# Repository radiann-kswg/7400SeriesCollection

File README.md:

# 7400 シリーズ汎用 IC Collection Database

7400 シリーズ汎用 IC の収集状況、購入履歴、データシート収集状況を管理する JSON データベースです。

## 📋 プロジェクト概要

このリポジトリは以下の目的で運用されています：

- **コレクション管理**: 入手済み IC の記録と管理
- **在庫追跡**: 所持している IC 型番の一覧化
- **購入計画支援**: レア度別の購入予定リスト
- **データシート管理**: メーカー別データシートの収集状況追跡
- **回路設計ナレッジベース**: 実際の使用例・回路設計情報の蓄積
- **汎用型番チートシート**: `74xNN` ごとの要点・注意点・一次資料確認の導線

## 🗂️ ディレクトリ構造

```
7400SeriesCollection/
├── overview/                             # overview系データ
│   ├── 7400_series_ic_overview.json      # マスターデータ：全IC情報
│   └── categories/                       # 上記マスタを論理分類で分割したJSON群
├── datasheets/                           # データシート管理
│   ├── 7400_series_ic_datasheet_collection_status.json
│   └── _download/                        # ダウンロード済みPDF保管
│       ├── FAIRCHILD(FairchildSemiconductor)/
│       ├── PHILIPS(NXPSemiconductors)/
│       ├── RENESAS/
│       ├── TI(TexasInstruments)/         # 型番プレフィックス別（直下に PDF は置かない）
│       │   ├── CD74HC/
│       │   ├── SN74/                     # 無印（標準 TTL）
│       │   └── SN74{ABT,AHC,ALS,AS,F,HC,LS,S}/
│       ├── TOSHIBA/
│       └── UTC(UnisonicTechnologies)/
├── getstarting/                          # 入手・購入管理【git 管理外】
│   ├── 7400_series_ic_collection_acquisition_history.json
│   ├── 7400_series_ic_purchase_plan_normal_or_lower.json
│   ├── 7400_series_ic_purchase_plan_rare.json
│   ├── 7400_series_ic_purchase_plan_maniac.json
│   └── 7400_series_ic_purchase_wishlist_very_nerd.json
├── scripts/                              # 自動化スクリプト
│   ├── autofill_gottenitems.py          # データシート情報自動同期
│   ├── merge_fp.py                      # データ統合処理
│   ├── refine_descriptions.py           # 説明文洗練化
│   ├── split_overview_by_logic_category.py # overviewを論理分類で分割
│   └── sort_datasheet_by_partnumber.py  # データシートソート
├── structures/                           # 【サブモジュール】回路構造資料（7400SeriesStructures）
└── usage/                                # 回路設計実例
  ├── 06_encoders_decoders/             # カテゴリ
  │   └── 74x141/                       # パーツ番号
  │       ├── 74x141.md                 # チートシート（自動生成）
  │       └── 01_simple_nixie_tube_demo.md  # 実回路例（手書き）
  └── A_combinated_samples/
    └── 74x181,182/                   # 複数IC連携サンプル（カンマ区切り）
```

## 📊 データファイル説明

### マスターデータ

#### `overview/7400_series_ic_overview.json`

全 7400 シリーズ IC の基本情報を格納するマスターデータベース。

```json
{
  "PartNumber": "74x00",
  "Description": "Quad 2-input NAND gate",
  "Description_JP": "4回路2入力NANDゲート",
  "Rarity": "Commons"
}
```

**レア度分類**:

- **一般流通品**: `Commons`, `Normal`, `Normal+`, `Rare`, `SuperRare`
- **廃止品/特殊品**: `Abolition(R+)`, `Maniac(SR+)`, `ManiacRare(SSR)`, `VeryNerd(UR)`

### 入手管理データ

> **⚠️ `getstarting/` は git 管理外です。** 購入先・コメントを含む私物情報のため、データシート PDF と同様に `.gitignore` で除外しています。ファイルはローカルに存在し、参照するスクリプトはそのまま動作します。クローンしただけの環境では存在しません。

#### `getstarting/7400_series_ic_collection_acquisition_history.json`

実際に入手した IC の記録（購入先、コメント含む）。

```json
{
  "PartNumber": "74x00",
  "GetStartingECS_JP": ["秋月電子", "Amazon"],
  "Comments": ["Amazonの74HCシリーズICキットから入手"],
  "GottenItemsMN_CMOS": ["74HC00N", "SN74HC00N"],
  "GottenItemsMN_TTL": ["SN74S00N"],
  "GottenItemsMN_Other": []
}
```

### データシート管理

#### `datasheets/7400_series_ic_datasheet_collection_status.json`

各パーツのデータシート入手状況を追跡。

```json
{
  "PartNumber": "74x00",
  "GottenItems_MakerOfDataSheet": {
    "SN74HC00N": "TI(Texas Instruments)",
    "74HC00N": "(収集予定:NXP Semiconductors)",
    "74S00N": "(保留)"
  }
}
```

**ステータス表記**:

- `"メーカー名"`: データシート入手済み
- `"(収集予定:メーカー名)"`: 未入手、収集予定
- `"(保留)"`: 収集保留中

## 🔧 スクリプト使用方法

### Python 開発環境とテスト

リポジトリルートで Python 3.14 の仮想環境を作成します。データ管理と PDF 処理の依存関係は `requirements.txt` に固定しています。基板配置に使う `pcbnew` と KiKit は KiCad 側の Python 環境で実行します。

**Windows（PowerShell）**。Python 本体を Codex からも読める場所に置くには、初回に Python Install Manager で次を実行します。

```powershell
py install --target=.venv/base 3.14
.\.venv\base\python.exe -m venv .venv
.\.venv\Scripts\python.exe -m pip install -r requirements.txt
```

作成済みの環境では、Codex・Copilot ともに次のコマンドでテストできます。VS Code の Python 拡張で別の環境が選択されている場合は、「Python: Select Interpreter」でこの実行ファイルを選択してください。

```powershell
.\.venv\Scripts\python.exe -m unittest discover -s scripts -v
```

**Linux（Codex・GitHub Copilot）**。`python3` と `venv` が利用できる環境で実行します。

```sh
sh scripts/setup-dev.sh
.venv/bin/python -m unittest discover -s scripts -v
```

Codex のクラウド環境でセットアップコマンドを指定する場合は `sh scripts/setup-dev.sh` を登録します。GitHub Copilot のクラウドエージェントでは、既定ブランチの [セットアップワークフロー](.github/workflows/copilot-setup-steps.yml) が同じコマンドを実行します。テストには公開データと一時ディレクトリを使います。

### データシート情報の自動同期

入手履歴からデータシート収集状況を自動生成：

```bash
python3 scripts/autofill_gottenitems.py
```

### データ統合処理

レア度別購入予定 JSON の生成：

```bash
python3 scripts/merge_fp.py
```

### マスターデータの論理分類分割

Wikipedia の 7400 シリーズ機能分類を参考に、`overview/7400_series_ic_overview.json` を分類別 JSON に分割して `overview/categories/` に出力します。

```bash
python3 scripts/split_overview_by_logic_category.py
```

出力される分類ファイル（例）:

- `01_buffers_inverters.json`
- `02_nand_and_gates.json`
- `03_nor_or_gates.json`
- `04_xor_xnor_gates.json`
- `05_flipflops_latches.json`
- `06_encoders_decoders.json`
- `07_data_selectors_mux_demux.json`
- `08_counters.json`
- `09_registers.json`
- `10_arithmetic.json`
- `11_error_detection_correction.json`
- `12_memory_storage.json`
- `13_programmable_logic.json`
- `14_system_controllers_timing.json`
- `15_interfaces_links.json`
- `16_analog_mixed_signal.json`
- `99_other.json`

````

### VS Code タスク

VS Code から実行可能なタスク：

- **Generate FP/ALL JSONs**: データ統合処理
- **Refine Descriptions**: 説明文洗練化
- **Regenerate ALL after refine**: 洗練後の再生成

※ これらのタスクは `scripts/merge_fp.py` / `scripts/refine_descriptions.py` を実行します。

## 📝 メーカー型番接頭辞

| 接頭辞               | メーカー                            |
| -------------------- | ----------------------------------- |
| `SN74*`, `CD74*`     | TI (Texas Instruments)              |
| `U74*`               | UTC (Unisonic Technologies)         |
| `HD74*`              | RENESAS                             |
| `TC74*`              | TOSHIBA                             |
| `MM74*`, `MC74*`     | FAIRCHILD (Fairchild Semiconductor) |
| `74HC*` (接頭辞なし) | PHILIPS (NXP Semiconductors)        |

## 🔗 参照リソース

- [List of 7400-series integrated circuits - Wikipedia](https://en.wikipedia.org/wiki/List_of_7400-series_integrated_circuits)
- [AGENTS.md](AGENTS.md) - 詳細な開発ガイドライン（Codex・Claude・Copilot 共通の単一の正本）

## 📐 回路設計例の作成

`usage/`ディレクトリに実際の回路設計例を追加できます。

### ディレクトリ命名規則

```text
usage/
└── {カテゴリ名}/
  └── 74x{型番}/
    ├── 74x{型番}.md  # チートシート（自動生成）
    ├── 01_*回路名.md
    ├── 02_*回路名.md
    └── ...
````

## 🧾 汎用型番チートシート（usage/{カテゴリ名}/{74xNN}/{74xNN}.md）

`overview/7400_series_ic_overview.json` を元に、汎用型番（`74xNN`）ごとのチートシートを生成します。

- 入口: [usage/index.md](usage/index.md)
- 生成スクリプト: [scripts/generate_usage_cheatsheets.py](scripts/generate_usage_cheatsheets.py)

```bash
python3 scripts/generate_usage_cheatsheets.py
```

方針: ピン配置/真理値表/電気特性などの断定は一次資料が必要なため、未検証のまま書かない（リンクとチェックリスト中心）。

複数 IC 連携のシリーズは `usage/A_combinated_samples/74x181,182/` のようにカンマ区切りでまとめる。

### 必須記載項目

1. 回路概要
2. 回路の仕様
3. ピンアサインと配線方法
4. 必要部品リスト
5. 配線の注意事項
6. 表示器の対応（LED、7 セグ、ニキシー管等）
7. 動作確認手順
8. トラブルシューティング
9. 回路の拡張性

詳細は [AGENTS.md の回路設計ドキュメント作成ガイド](AGENTS.md#回路設計ドキュメント作成ガイドusage)を参照。

## 🔌 デモ基板の製作（`pcb-demo/`）

収集した現物の DIP IC をソケットに挿し、**その IC が実際に動いている状態**で展示する基板群。
「本物の元素を封入した周期表」の 7400 シリーズ版という位置づけ。

全タイルで回路トポロジは共通で、型番ごとに変わるのは**電源ピン配線・未実装セル・シルクの 3 点だけ**。
これにより、ピン機能表が未確定の型番でも「VCC/GND のピン位置とピン数」さえ一次資料で確認すれば設計できる。

| ドキュメント | 内容 |
|---|---|
| [`pcb-demo/REQUIREMENTS.md`](pcb-demo/REQUIREMENTS.md) | 要件定義（決定事項・制約・段階計画・非目標・リスク） |
| [`pcb-demo/_carrier/README.md`](pcb-demo/_carrier/README.md) | 共通キャリア設計仕様（回路方式・定数・命名規則・生成規則） |
| [`pcb-demo/ORDER_CHECKLIST.md`](pcb-demo/ORDER_CHECKLIST.md) | JLCPCB 発注チェックリスト（発注ゲート） |
| [`pcb-demo/index.md`](pcb-demo/index.md) | 型番別 KiCAD プロジェクト一覧 |

## 🛡️ データ整合性の維持

このプロジェクトは複数の JSON ファイル間で整合性を保つ必要があります：

- **PartNumber**: すべてのファイルで`74x`形式を使用
- **文字エンコーディング**: UTF-8 を厳守
- **配列順序**: PartNumber 昇順を維持
- **型番表記**: 汎用表記（`74x00`）と実際の型番（`SN74HC00N`）を区別

## 🚫 禁止事項

1. 既存データの意図しない改変
2. PartNumber 体系の破壊（`74x`形式の維持）
3. 文字コードの変更（UTF-8 厳守）
4. JSON スキーマの勝手な変更
5. ファイル間の不整合を引き起こす操作

## 📄 ライセンス

MIT License（[LICENSE](LICENSE)）。

**ハードウェア設計データ（`pcb-demo/` 配下の KiCAD プロジェクト・Gerber・BOM を含む）も同じく MIT License** で提供します。

---

**管理者**: radiann-kswg
**最終更新**: 2026 年 2 月 14 日

```

```

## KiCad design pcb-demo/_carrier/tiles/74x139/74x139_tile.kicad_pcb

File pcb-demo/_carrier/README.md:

# 共通キャリア設計仕様（Specimen Tile v0.1）

全タイルで共通の回路トポロジ。型番ごとに変わるのは**電源ピン配線・未実装セル・シルクの 3 点だけ**（→ [`../REQUIREMENTS.md`](../REQUIREMENTS.md) §2.3）。

- 版: 0.8（2026-11-22: プルアップ LED セル（active_low / open_collector 出力）の +5V を裏面経由に変更（REQUIREMENTS D31）。クロックセルは接点 1・11 のみ（D30、R10））。0.7（2026-11-22: オープンコレクタ出力を赤 LED + プルアップ配線で表示（REQUIREMENTS D29））。0.6（2026-09-17: 入力接点の LED 表示を廃止しスイッチのみに変更（REQUIREMENTS D25）。2026-09-16: Rd を 220Ω に変更（旧 1kΩ、REQUIREMENTS D16）。LED を負論理=赤／通常=白の2色に変更（D22）。クロック入力クリーンアップ回路（タクトスイッチ+RC+74x1G14）を実装・DRC/ERC検証済み（REQUIREMENTS §4.2/D17・D24））
- 対象: DIP-14 / DIP-16 / DIP-20（300mil）= 所持品の 118/120

---

## 1. ブロック構成

```text
        +5V ──┬──────────────────────────────── 電源ピン（型番依存）
              │
             C1 100nF
              │
        GND ──┴──────────────────────────────── GND ピン（型番依存）

  ┌─ I/O セル（信号ピン 1 つあたり。最大 18 セル）──────────┐
  │                                                          │
  │   +5V ──o                                                │
  │          \  SW（SPDT）                                   │
  │   GND ──o  \___ Rd 1k ───┬─── ソケット接点 k ─── IC ピン │
  │                          │                               │
  │                          └─ Rled 4.7k ─ LED ─ GND        │
  └──────────────────────────────────────────────────────────┘
```

---

## 2. I/O セルの回路方式

### 2.1 採用案: SPDT スイッチ + 直列抵抗（プルダウン無し）

スイッチで入力を **+5V か GND のどちらかに必ず接続**し、間に 220Ω を挟む（旧 1kΩ、REQUIREMENTS D16）。

**この方式を採る理由（D10 からの変更）**: 要件定義 D10 で想定した「SPST スイッチ + 10kΩ プルダウン」は、**TTL ファミリで成立しない**。74LS の入力は L のとき最大 0.4mA を吐き出すため、10kΩ プルダウンでは入力電圧が 0.4mA × 10kΩ = 4V まで浮き、VIL(max) 0.8V を大きく超えて L と認識されない。SPDT なら L 側でも 1kΩ を介して GND に落ちるため 0.4V に収まり、**CMOS と TTL の両方が動く**。副次的に、プルダウン抵抗 18 本が不要になり部品点数もむしろ減る。

### 2.2 定数と動作点

| 記号   | 値    | 役割                     |
| ------ | ----- | ------------------------ |
| `Rd`   | 220 Ω | 入力駆動の直列抵抗（旧 1kΩ、D16） |
| `Rled` | 4.7 kΩ | LED 電流制限             |
| LED    | 0603 赤（高効率品） | 状態表示   |

計算（VCC = 5V、LED 順方向電圧 Vf ≈ 2.0V）:

| 条件                           | 結果      | 判定                                                |
| ------------------------------ | --------- | --------------------------------------------------- |
| スイッチ H 側（LED 負荷込み）  | 約 4.4V   | 74HC VIH 3.5V / 74LS VIH 2.0V を満たす              |
| スイッチ L 側（74LS の IIL 0.4mA、Rd=220Ω） | 約 0.09V  | VIL(max) 0.8V を満たす（旧 1kΩ では 0.4V。220Ω化でマージン拡大、S/H 系の大きい IIL にも対応、D16） |
| IC 出力が H のときの LED 電流  | 約 0.62mA | 高効率 LED なら室内で視認可。Phase 1 で実物調整     |
| **出力ピンのスイッチを誤操作したときの電流（Rd=220Ω）** | **約 22.7mA（公称）/ 約 25.1mA（Vcc+5%・R-5%の最悪条件）** | **要注意**: 74HC 絶対最大定格 ±25mA に対しほぼ余裕が無く、最悪条件では超過し得る。1% 級抵抗の使用、またはパイロットに含む各ファミリの個別データシートでの再確認を推奨（発注前の宿題） |

**安全規則**: `Rd` は**出力ピンや双方向ピンを誤って駆動したときの電流制限器を兼ねる**ため、**省略は禁止**。現行値は 220Ω固定（D16）で、上表の通り 74HC 絶対最大定格に対するマージンが小さいため、これより**低い値への変更は不可**（誤操作時の電流がさらに増える）。出力接点はスイッチと `Rd` を DNP にする（REQUIREMENTS D15）が、フットプリントは残す。

### 2.3 廉価案（TTL 非対応）

SPDT スイッチの単価が見積もりを圧迫する場合のみ、**SPST + 10kΩ プルダウン**に落とす。この場合 **TTL（LS/S/ALS/F/H）ファミリは動作対象外**となり、CMOS（HC/HCT/AC/ACT/AHC/LVC）専用になる。採否は Phase 1 の LCSC 価格確認で判断する。

---

## 3. 部品構成（1 タイル）

| Ref            | 部品                        | 数         | 実装       |
| -------------- | --------------------------- | ---------: | ---------- |
| `U1`           | DIP-20 ソケット 300mil       |          1 | **手はんだ** |
| `J1`           | 2 ピンヘッダ 2.54mm（+5V/GND） |          1 | **手はんだ** |
| `D1`–`D20`     | LED 0603（`active_low` 出力=赤 C2286 / 通常出力=白・部品番号未選定。D22） | 最大 18 | JLCPCB |
| `R1`–`R20`     | `Rled` 4.7kΩ 0603（C23162）   | 最大 18    | JLCPCB     |
| `R21`–`R40`    | `Rd` 220Ω 0603（部品番号未選定、実装確定時に選定。D16） | 最大 18 | JLCPCB |
| `SW1`–`SW20`   | SPDT スイッチ MSS12C02LS-BB2.0（C3008585） | 最大 18 | JLCPCB  |
| `C1`           | 100nF 0603（C14663）          |          1 | JLCPCB     |

SMD 実装点数は最大約 61。**抵抗を 4 素子アレイにまとめると 36 → 9 個に減り、合計約 34 点**になる（→ REQUIREMENTS §5）。アレイも Basic で揃うが、50×50mm では個別 0603 で収まったため現状は個別（REQUIREMENTS D14）。スイッチだけが Extended。

抵抗値は `Rled` と `Rd` の 2 種類のみ。部品種類を増やさないこと。

---

## 4. リファレンス指定子の命名規則

生成スクリプトが機械的に参照できるよう、**ソケット接点番号 k（1〜20）と 1 対 1 に対応させる**:

| 部品         | Ref     |
| ------------ | ------- |
| スイッチ     | `SWk`   |
| LED          | `Dk`    |
| `Rled`       | `Rk`    |
| `Rd`         | `R(20+k)` |
| ソケット接点 | `U1` パッド `k` |

例: 接点 7 → `SW7` / `D7` / `R7` / `R27` / `U1` パッド 7。

この規則を崩すと型番別生成（電源接点の差し替えと DNP 指定）が成立しないため、**手作業で振り直さないこと**。

---

## 5. 寸法・レイアウト規約

| 項目               | 値                                       |
| ------------------ | ---------------------------------------- |
| 外形               | 50 × 50 mm（100×100mm パネルに 2×2。REQUIREMENTS D9） |
| 層数 / 厚み / 銅箔 | 2 層 / 1.6mm / 1oz                       |
| 最小パターン幅     | 0.25mm（JLCPCB 下限 0.127mm には張り付かない） |
| 基板端クリアランス | 銅箔は端から 0.5mm 以上（V-cut 分離のため） |
| 実装面             | **上面のみ**（Economic 組立の制約）      |
| `U1` 配置          | タイル中央に横置き。ピン 1 を左下（接点 1〜10 が下段、20〜11 が上段） |
| `C1` 配置          | ソケット左の `J1` 横。標準配置の VCC（接点 20）から約 4mm。非標準の型番（§6.4）では離れる |
| I/O セル配置       | 接点 k の列を 4.6mm ピッチで並べる（下段は接点 1→10、上段は 20→11 を左から）。1 列は外周側から スイッチ → LED / `Rk` / `R(20+k)` → ソケットへの引き出し |
| 電源               | +5V は外周レール（上・下・左）とソケット下を通るバス。GND は裏面ベタ |
| シルク             | 各列のピン名（VCC/GND 含む）、型番・機能名（英・和）、給電表示。裏面に版・カテゴリ・ライセンス |

I/O セルは接点順に規則的に並べる。これにより自動配線が不要になり（→ REQUIREMENTS §9 R5）、シルクのピン名とも視覚的に対応する。

---

## 6. 型番別の生成規則

### 6.1 接点マッピング

n ピン IC をピン 1 側へ端寄せして挿入する前提:

```text
IC pin i  (i <= n/2)  ->  ソケット接点 i
IC pin i  (i >  n/2)  ->  ソケット接点 i + (20 - n)
```

### 6.2 差分の適用

| 差分         | 規則                                                                                     |
| ------------ | ---------------------------------------------------------------------------------------- |
| ① 電源接点   | 型番の VCC / GND ピンを §6.1 で接点に変換し、その接点を +5V / GND ベタに接続。**I/O セルは実装しない** |
| ② セル種別   | `pinspec/{型番}.json` の `dir` で決める。`input` → **スイッチのみ**（`Rk`・`Dk` を DNP、REQUIREMENTS D25）。`output` / `tri_state` → `SWk`・`R(20+k)` を DNP（LED のみ）。`open_collector` → LED のみで、`active_low` 出力と同じ赤 LED + プルアップ配線（点灯 = L、REQUIREMENTS D29）。`bidirectional` は D19 により生成停止。未使用接点・`nc` → 全部 DNP。DNP は BOM・CPL から除外 |
| ③ シルク     | 汎用型番・機能名（EN / JP）・カテゴリ・各接点のピン名                                    |

### 6.3 実装セル数

| パッケージ | 実装する I/O セル |
| ---------- | ----------------: |
| DIP-14     | 12                |
| DIP-16     | 14                |
| DIP-20     | 18                |

### 6.4 電源ピンが非標準の型番

[`../REQUIREMENTS.md`](../REQUIREMENTS.md) §2.5 の 4 型番（74x73 / 74x75 / 74x90 / 74x93）は VCC/GND が角ピンにない。生成時に**一次資料で個別確認**すること。角ピン決め打ちのロジックを書かない。

---

## 7. 設計上の禁止事項

1. `Rd` の省略・220Ω 未満への変更（§2.2 の安全規則。現行値は D16 で 220Ω に固定）
2. §4 のリファレンス命名規則を崩すこと
3. 抵抗値を 2 種類より増やすこと
4. 裏面への SMD 部品配置（Economic 組立は上面のみ）
5. 電源ピン位置を「角ピン」と決め打ちすること（§6.4）
6. 一次資料で VCC/GND・ピン方向を確認していない（`pinspec` の無い）型番のタイルを発注対象に入れること

---

## 8. Phase 1 で決めること

- [x] SPDT スイッチの LCSC 部品と単価 → MSS12C02LS-BB2.0（C3008585）500 個以上 $0.0669。廉価案には落とさない
- [x] 抵抗アレイ化の可否 → Basic あり（C20197 / C1980、旧 Rd=1kΩ 時点の参考値。D16 で Rd を 220Ω に変更したため C20197 は非対応）。配置が収まったので個別 0603
- [ ] LED の実物輝度（0.62mA で視認できるか。不足なら `Rled` を下げ、§2.2 の動作点を再計算する）
- [x] 33 × 50mm に上面のみで全部品が収まるか → 収まらない。50 × 50mm に変更（REQUIREMENTS D9）
- [x] パネライズの手段 → KiKit 採用・DRC 0 で検証済み（REQUIREMENTS §9 R6）
- [x] MSS12C02LS のランド・位置決め穴を SHOU HAN 純正図面 C3008585 で照合し `.kicad_mod` を修正（2026-09-16）。残: 4隅 SH パッド・外形は MSK12C02 流用値のまま（概算とは近似）、H/L 向きシルクは未追加、現物サンプルでの最終確認は未実施（REQUIREMENTS §9 R8）
- [x] `Rd` 220Ω の LCSC 部品番号 → UNI-ROYAL 0603WAF2200T5E（C22962）
- [x] 通常出力用 白 LED の LCSC 部品番号 → Hubei KENTO KT-0603W（C2290）
- [x] クロック入力クリーンアップ回路（タクトスイッチ + RC + 74x1G14）の定数設計・部品選定 → RC=10kΩ/1µF、SWT=EVQP2R02M(C79161)、RCK=10kΩ(C25804)、CCK=1µF(C106248)、UG=SN74LVC1G14DBVR(C7835)。`generate_specimen_tile.py` に実装、DRC/ERC検証済み（REQUIREMENTS §4.2/D17・D24）
- [ ] 実見積もり

---

## 9. 生成

```powershell
& 'C:\Program Files\KiCad\10.0\bin\python.exe' scripts\generate_specimen_tile.py 74x00 74x244 74x273
```

- 出力: `tiles/{型番}/{型番}_tile.kicad_{sch,pcb,pro}`、専用フットプリント `Specimen.pretty/`
- ピン数・VCC/GND・各ピンの方向は `pinspec/{型番}.json` から読む（作り方は REQUIREMENTS §4.1）。無い型番はエラーで止まる
- 仕様を変えるときはスクリプトを直して再生成する。生成物を手で編集しない
- 検証: `kicad-cli sch erc --severity-all` と `kicad-cli pcb drc --severity-all --schematic-parity`

---

## 関連ドキュメント

- 要件定義: [`../REQUIREMENTS.md`](../REQUIREMENTS.md)
- 発注チェックリスト: [`../ORDER_CHECKLIST.md`](../ORDER_CHECKLIST.md)

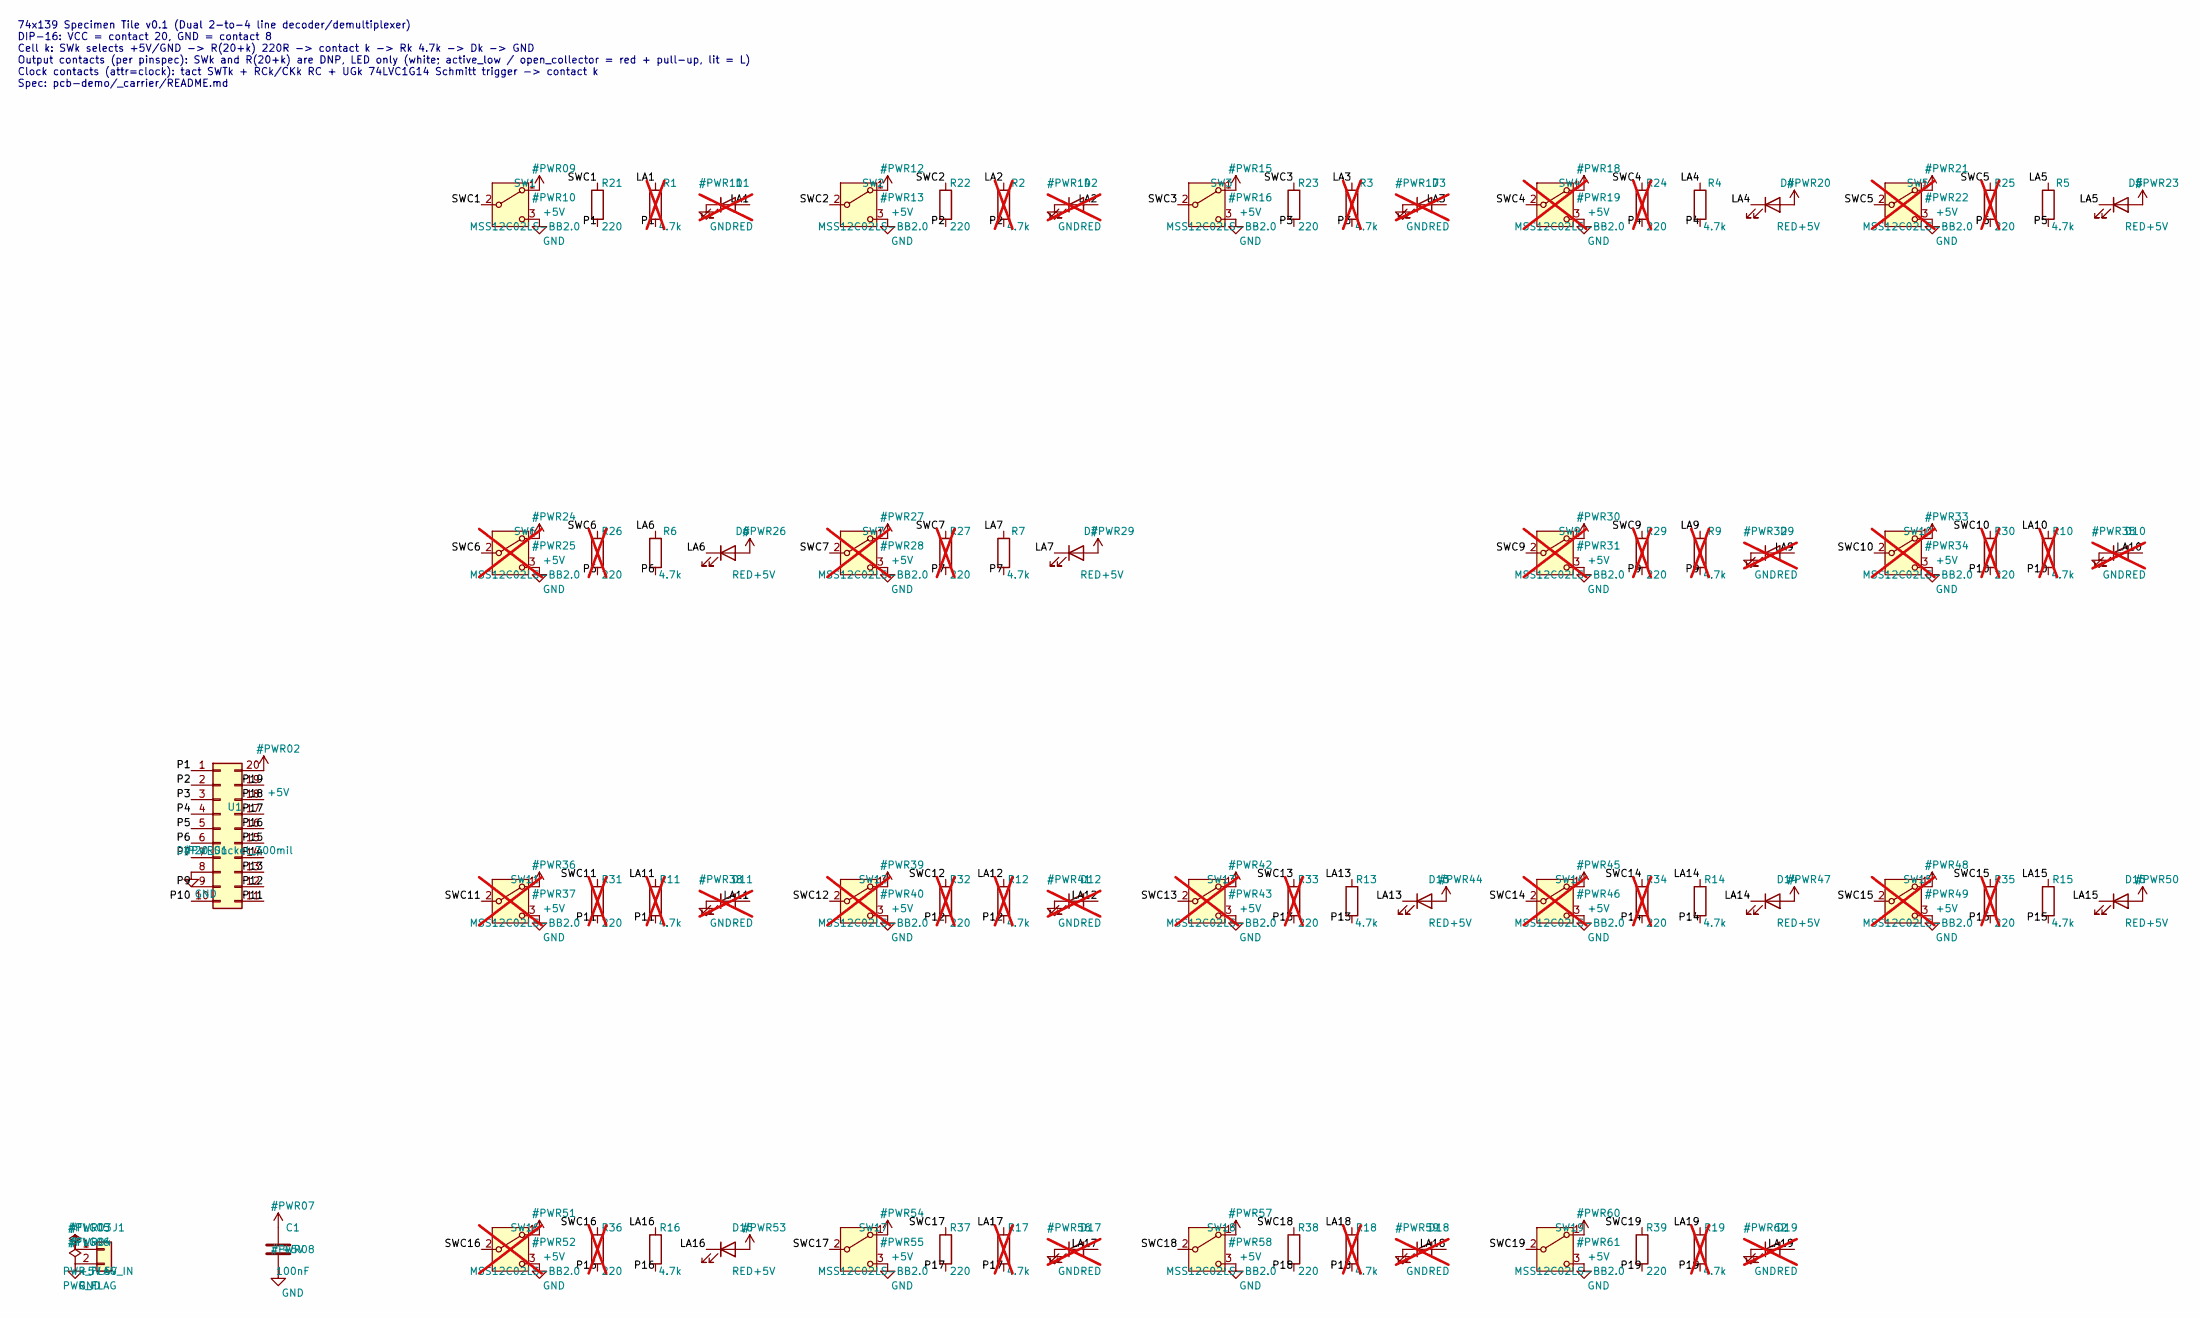
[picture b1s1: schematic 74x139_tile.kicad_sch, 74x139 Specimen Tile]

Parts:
C1: 100nF; C_0603_1608Metric; MPN CC0603KRX7R9BB104; LCSC Part # C14663
D1, D2, D3, D9, D10, D11, D12, D17, D18, D19: RED; LED_0603_1608Metric; MPN KT-0603R; LCSC Part # C2286; not fitted
D4, D5, D6, D7, D13, D14, D15, D16: RED; LED_0603_1608Metric; MPN KT-0603R; LCSC Part # C2286
J1: 5V_IN; PinHeader_1x02_P2.54mm_Vertical
R1, R2, R3, R9, R10, R11, R12, R17, R18, R19: 4.7k; R_0603_1608Metric; MPN 0603WAF4701T5E; LCSC Part # C23162; not fitted
R4, R5, R6, R7, R13, R14, R15, R16: 4.7k; R_0603_1608Metric; MPN 0603WAF4701T5E; LCSC Part # C23162
R21, R22, R23, R37, R38, R39: 220; R_0603_1608Metric; MPN 0603WAF2200T5E; LCSC Part # C22962
R24, R25, R26, R27, R29, R30, R31, R32, R33, R34, R35, R36: 220; R_0603_1608Metric; MPN 0603WAF2200T5E; LCSC Part # C22962; not fitted
SW1, SW2, SW3, SW17, SW18, SW19: MSS12C02LS-BB2.0; SW_SPDT_Shouhan_MSS12C02LS; MPN MSS12C02LS-BB2.0; LCSC Part # C3008585
SW4, SW5, SW6, SW7, SW9, SW10, SW11, SW12, SW13, SW14, SW15, SW16: MSS12C02LS-BB2.0; SW_SPDT_Shouhan_MSS12C02LS; MPN MSS12C02LS-BB2.0; LCSC Part # C3008585; not fitted
U1: DIP20_Socket_300mil; DIP-20_W7.62mm_Socket

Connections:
+5V: C1.1, D4.2 (A), D5.2 (A), D6.2 (A), D7.2 (A), D13.2 (A), D14.2 (A), D15.2 (A), D16.2 (A), J1.1, SW1.1 (A), SW2.1 (A), SW3.1 (A), SW4.1 (A), SW5.1 (A), SW6.1 (A), SW7.1 (A), SW9.1 (A), SW10.1 (A), SW11.1 (A), SW12.1 (A), SW13.1 (A), SW14.1 (A), SW15.1 (A), SW16.1 (A), SW17.1 (A), SW18.1 (A), SW19.1 (A), U1.20
/LA1: D1.2 (A), R1.1
/LA2: D2.2 (A), R2.1
/LA3: D3.2 (A), R3.1
/LA4: D4.1 (K), R4.1
/LA5: D5.1 (K), R5.1
/LA6: D6.1 (K), R6.1
/LA7: D7.1 (K), R7.1
/LA9: D9.2 (A), R9.1
/LA10: D10.2 (A), R10.1
/LA11: D11.2 (A), R11.1
/LA12: D12.2 (A), R12.1
/LA13: D13.1 (K), R13.1
/LA14: D14.1 (K), R14.1
/LA15: D15.1 (K), R15.1
/LA16: D16.1 (K), R16.1
/LA17: D17.2 (A), R17.1
/LA18: D18.2 (A), R18.1
/LA19: D19.2 (A), R19.1
/P1: R1.2, R21.2, U1.1
/P2: R2.2, R22.2, U1.2
/P3: R3.2, R23.2, U1.3
/P4: R4.2, R24.2, U1.4
/P5: R5.2, R25.2, U1.5
/P6: R6.2, R26.2, U1.6
/P7: R7.2, R27.2, U1.7
/P9: R9.2, R29.2, U1.9
/P10: R10.2, R30.2, U1.10
/P11: R11.2, R31.2, U1.11
/P12: R12.2, R32.2, U1.12
/P13: R13.2, R33.2, U1.13
/P14: R14.2, R34.2, U1.14
/P15: R15.2, R35.2, U1.15
/P16: R16.2, R36.2, U1.16
/P17: R17.2, R37.2, U1.17
/P18: R18.2, R38.2, U1.18
/P19: R19.2, R39.2, U1.19
/SWC1: R21.1, SW1.2 (B)
/SWC2: R22.1, SW2.2 (B)
/SWC3: R23.1, SW3.2 (B)
/SWC4: R24.1, SW4.2 (B)
/SWC5: R25.1, SW5.2 (B)
/SWC6: R26.1, SW6.2 (B)
/SWC7: R27.1, SW7.2 (B)
/SWC9: R29.1, SW9.2 (B)
/SWC10: R30.1, SW10.2 (B)
/SWC11: R31.1, SW11.2 (B)
/SWC12: R32.1, SW12.2 (B)
/SWC13: R33.1, SW13.2 (B)
/SWC14: R34.1, SW14.2 (B)
/SWC15: R35.1, SW15.2 (B)
/SWC16: R36.1, SW16.2 (B)
/SWC17: R37.1, SW17.2 (B)
/SWC18: R38.1, SW18.2 (B)
/SWC19: R39.1, SW19.2 (B)
GND: C1.2, D1.1 (K), D2.1 (K), D3.1 (K), D9.1 (K), D10.1 (K), D11.1 (K), D12.1 (K), D17.1 (K), D18.1 (K), D19.1 (K), J1.2, SW1.3 (C), SW2.3 (C), SW3.3 (C), SW4.3 (C), SW5.3 (C), SW6.3 (C), SW7.3 (C), SW9.3 (C), SW10.3 (C), SW11.3 (C), SW12.3 (C), SW13.3 (C), SW14.3 (C), SW15.3 (C), SW16.3 (C), SW17.3 (C), SW18.3 (C), SW19.3 (C), U1.8

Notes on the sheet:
74x139 Specimen Tile v0.1 (Dual 2-to-4 line decoder/demultiplexer) DIP-16: VCC = contact 20, GND = contact 8 Cell k: SWk selects +5V/GND -> R(20+k) 220R -> contact k -> Rk 4.7k -> Dk -> GND Output contacts (per pinspec): SWk and R(20+k) are DNP, LED only (white; active_low / open_collector = red + 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

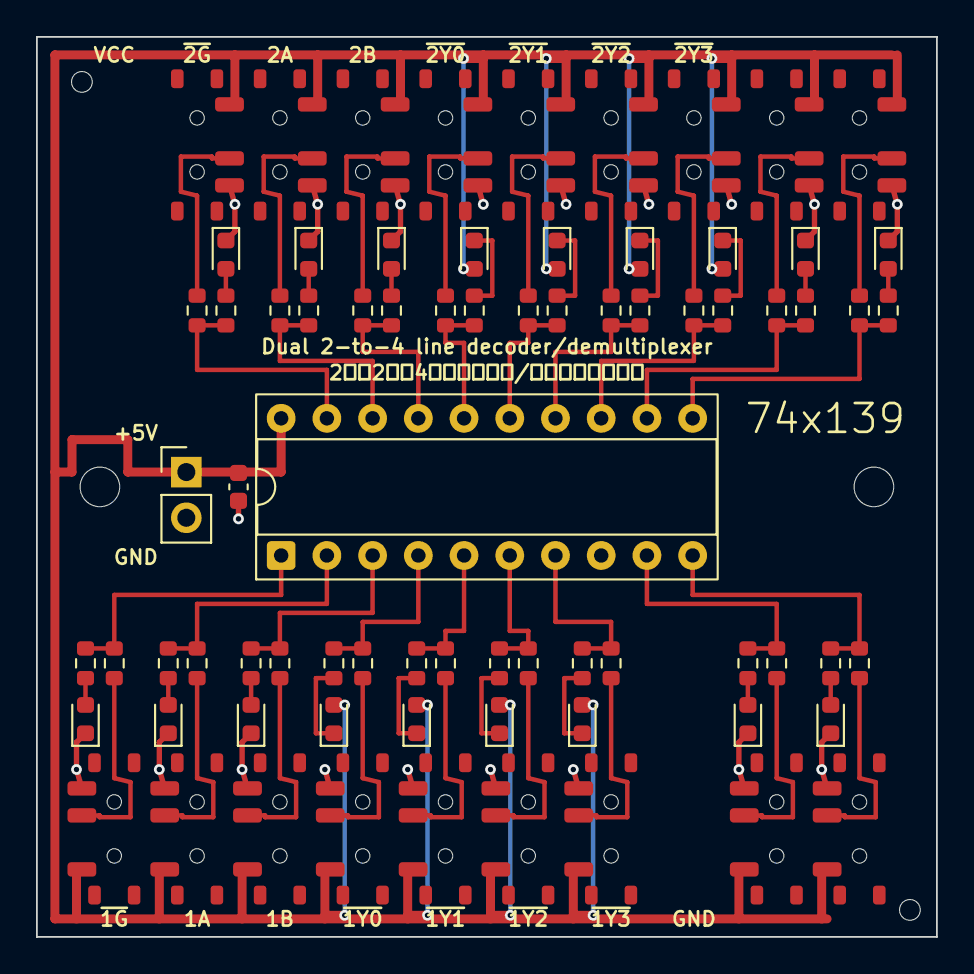
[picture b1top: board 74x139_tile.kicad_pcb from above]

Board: 2 copper layers, 50.0 x 50.0 mm, 79 parts (0 on the bottom side), 56 nets.

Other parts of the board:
MTG1, MTG2: MountingHole_2.2mm_M2
TH1, TH2: ToolingHole_1.152mm

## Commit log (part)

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2025-08-29 Init
2025-08-29 Rarity精査
    Copilot君にフィードバックしてもらった（※人件費の削減）
2025-08-30 購入状況更新
    - マルツ(第１波)・共立エレショップでまとめ買いした商品が着弾したので入手ICの型番を更新（同時に、未着弾(配送中)は空欄に変更）
    - 購入予定(`FP: futureplan`)のパーツを別ファイルに追加
2025-08-31 諸々情報更新
    - レアリティ・入手先まわりを更新
    - ALU(`74x181`,`74x381`)が配送中に関税引っかかったっぽそうな件を特記
    - Mouser Japanから入手可能なものを可能な限りfuture planに追加（まだめっちゃありそう）
2025-09-01 購入状況更新
    - Mouserで購入したパーツを追記
    （空いてるフィールドはこの後Copilotと埋める）
    - ALU他が着弾したので所有中の型番についての情報を追記
2025-09-01 Copilotで鑑定
    - Mouserで新規購入したものについてCopilotで仕様概要とレアリティを入力してもらった（一応マニア向けのパーツは今回含まれないので`"Normal+"`か`"Rare"`がメイン）
    - Mouserで購入したものをfuture planから除外
2025-09-05 購入状況更新・gitignore更新
    ### 購入状況更新
    - Mouserでまとめ買いした商品が着弾したので入手ICの型番を更新
    - 細々とした情報修正
    ### gitignore更新
    - データシートの保存用フォルダを作成してgitignoreに追記
    - MacOSでの更新で`.DS_Store`が変更ステージに追加されるのでこれも追記
2025-09-05 購入状況更新 続き
    マルツ, eBayで購入/再購入したパーツを追記
    - ALUおよびその補助ロジック(eBay)
    - 拡張可能ゲート(eBayよりキリル型番互換品を購入, futurre plan記載あり)
    - マルチプレクサ（マルツにて再購入）
2025-09-06 購入状況更新
    - マルツ(第２波)・秋月（第２波）でまとめ買いした商品が着弾したので入手ICの型番を更新
    - 誤記修正
2025-09-06 フィールド名変更
    もうちょっとわかりやすい命名に変更
2025-09-06 Rarity精査
    Copilot君に精査させたら誤記が見つかったので修正
2025-09-09 購入状況更新
    - eBayで購入した商品が着弾したので入手ICの型番を更新
    - レアリティ推敲
    - キリル型番の互換品を入手したものはその旨を追記
2025-09-10 `DS_Store`をgitから除外
2025-09-13 購入状況更新
    - eBayで袋詰め卸売されたもの(第１波)が着弾したので入手できたICを追加・レアリティ査定
    - このグラブパックで`"Rare"`以下の新規入手があった分については他の入手可能ECSを調査しFPに追記
    - ついでに細かい入手方法の記載を文面調整
2025-09-13 購入状況更新 続き
    詰め合わせなどでしか購入していないパーツ周辺の相場状況を軽く調べてから入手できそうなものを購入
    - Mouserで購入(第２波)した商品を追記（一部FP）
    - Mouserで在庫を確認したが所持数的に購入しなかったものをFPに追記
    - 相場状況を鑑みて一部の`Rarity`を調整
    - 型番追記漏れを修正
2025-09-13 データ構成改装
    - `Description`などのパーツ概要を別JSONファイルに分け、複数ファイルにフィールドを重複して記入されないように
    - データシート収集状況のJSONファイルを追加
2025-09-13 データ自動拡張 その１
    - `.vscode`フォルダ追加(Copilot運用のため)
    - Copilotを酷使してwikiページから`74x832`までのパーツ情報を全て取得させた
2025-09-13 データ自動拡張 その２
    パッチ周りの途中データをGitにロギング（なんか後で途中データ消すと不味そうだったので）
2025-09-13 データ自動拡張 その３－１
    ファイル移動（CopilotがGit参照して復元できるようロギングしておく）
2025-09-13 データ自動拡張 その３－２
    一応これでCopilot処理中に万が一のことがあっても大丈夫……なはず
2025-09-13 データ自動拡張 その３－３
    なんか残ってた
2025-09-13 データ構成改装 その２
    ディレクトリ構成・ファイル名推敲
2025-09-13 Rarity精査
    ベリーナード(`VeryNerd(UR)`)級の~~入手性をちょっと舐めて掛かってたので~~水準を調整
2025-09-17 内容を精査
2025-09-17 内容を精査 その２
2025-09-17 フューチャープラン見直し
2025-09-17 ファイル名推敲
2025-09-17 データ構造変更
    所持状況の型番をCMOS,TTL,その他でフィールド分けした（使用用途の選定のため）
2025-09-17 データ構造変更 その２
    使用済のスクリプトを移動
2025-09-20 購入状況更新 wip-eBay袋詰め第２波①
    - eBayで袋詰め卸売されたもの(第２波)が着弾したので入手できたICを追加（※途中）
    - データシート収集用の型番転記スクリプトをCopilot君に提案されたので実装・実行（ついでにデータシート収集先で保留になってるものをできる範囲で型番からメーカ推定してもらった）
2025-09-20 フューチャープラン見直し その１
2025-09-21 Rarity精査
2025-09-21 フューチャープラン見直し その２
    FPファイルを４ファイルに細分化
2025-09-21 フューチャープラン見直し その３
    保存し忘れてた
2025-09-23 データ整備
    TTL系なのに`GottenItemsMN_TTL`に入力されてない型番（標準TTL：`74xx`）を修正
2025-09-23 購入状況更新 wip-eBay袋詰め第２波②
    - eBayで袋詰め卸売されたもの(第２波)が着弾したので入手できたICを追加（※続き）
    - eBayで購入したとしても出品者がJAMECOだった場合はJAMECOとして購入先を指定するように（海外の正式な半導体販売店のため）
    ### 将来対応（※予定メモ）
    - `74x1000`,`74x5074`などの４桁番号のパーツ概要追加
2025-09-23 データ自動拡張 その１
    `74x1032`までとりあえずCopilot君に出力してもらった
2025-09-23 データ自動拡張 その２
2025-10-17 購入状況更新 wip-eBay袋詰め第２波③
    - eBayで袋詰め卸売されたもの(第２波)が着弾したので入手できたICを追加（※続き）
    ### 将来対応（※予定メモ）
    - `74x1244`などの４桁番号のパーツ概要追加
2025-10-30 購入状況更新 eBay単品
2025-10-30 購入状況更新 Mouser単品
2025-10-30 データシート収集状況更新
    ついでに番号順に並び替えるスクリプトを実装
2025-10-30 Rarity精査 他
2025-11-10 Usage追加
    74x181,182の実演回路を提案してもらった
2025-11-10 Usage追加
    74x141の実演回路を提案してもらった
2025-11-10 Update copilot-instructions.md
    色々ごちゃついてきたのでリファクタリング
2025-11-20 データ構造拡張
    - データシートをGitに含めるよう`.gitignore`の仕様を変更
    - 指示書周り追記
    - `README.md`追加
2025-12-20 ファイル名称をASCII半角文字に統一
2025-12-20 論理カテゴリ分類 その１
2025-12-20 論理カテゴリ分類 その２
    ディレクトリ構成を推敲
2025-12-20 論理カテゴリ分類 その３
    `Category`フィールド追加で素引き可能に
2025-12-20 データシート収集状況更新
    74x182のデータシートを収集してたものの追記し忘れてたので
2025-12-20 論理カテゴリ分類 その４
    Copilot君のカテゴライズを推敲したところ
    - 拡張器とキャリー生成器は新規カテゴリで分類できる
    - 一部ベリーナード級のALUに分類漏れがある
    ことが判明したのでこれを強化してもらった~~（自力添削もできなくはないけど）~~
2025-12-20 古いデータを削除
2025-12-20 Copilot指示強化 その１ ＆ Usage添削 その１
    実際に`./usage/74x181,182`で提案された回路案を実践したらピンアサインとかデータシートと全く合致しなかったので、今後はより情報収集を強化しデータシートも参照するようCopilot君を調教した
    余談：74x63のロジック概要がよくわからなかったので調べるついでにChatGPTでGPT-5.2を試してみたところ、割と真剣に情報を収集しながら思考してくれてそうなので ちゃんと調教すれば今後こういうミスが将来的に減ってくるのかもしれない…？
2025-12-20 Usage添削 その２
2025-12-20 Copilot指示強化 その２
    ロール指定やパーツ運用のあれこれを指示書に追記してもらった
    `./.temp`内を自動削除してもらう文面は自力で追記
2025-12-20 Usage添削 その３
2026-02-14 大幅改修・チートシート生成 その１
    ### `usage-renewal`ブランチ概要
    リポジトリ全体を改修することになりそうなので以後ローカル環境での作業ブランチで対応
    Copilot君によりCopilot君が「各ロジックパーツのチートシート自動生成」と「データシートのダウンロードによるファクトチェックの手間削減」を実現するのが最終目標
    完全な成功を確認次第 メインブランチにマージして正式にローンチしていく予定
    ### Copilotの指示内容・リポジトリ構成更新
    MITライセンス適応想定に方針変更
2026-02-14 大幅改修・チートシート生成 その２
    - データシート自動取得の下準備
    - 指示書にタスクを明記
2026-02-14 大幅改修・チートシート生成 その３
    データシートの自動参照スクリプトを確実なものになるよう推敲
2026-02-14 大幅改修・チートシート生成 その４
    Usageファクトチェック用のフッター追記機能を実装
    - データシートとUsageの記載に齟齬がないかについての機能
    - とりあえずUsageが現存するパーツ`74x141,181,182`で試運転
2026-02-14 大幅改修・チートシート生成 その５
    所持してる型番の入手履歴からデータシートを取得するよう半自動化スクリプトを調整（途中）
    - 現状はまずTI(Texas Industry)製のものだけを取得可能かどうか確認
    - PDF形式でないものや`404(Not Found)`の応答が来るものといった42の品番は確認対象でも取得に失敗しているらしい
2026-02-14 大幅改修・チートシート生成 その６
    ### 更新内容
    - いったん作業ログを作成するよう指示
    - 大規模改修時は作業ログを取るよう指示書を更新
    ### 主な理由
    - 作業ログの作成をさせる指示がまだだったため
    - もともとHDDドライブで行っていたがあまりにも高度な処理と判断し、SSDにローカル環境を移動することにしたため
2026-02-14 ローカル環境移動・引継ぎ
    もともとHDDドライブで行っていたがあまりにも高度な処理と判断し、SSDにローカル環境を移動することにしたため（※リマインド引用）
    引継ぎ直前のコミット >> `a9a1dbe3005a11a0455cb7e29dba5c799ff5e24c`
2026-02-14 ローカル環境移動・引継ぎ その２
    ログフォルダが２つになってたので統合
2026-02-14 大幅改修・チートシート生成 その３
    実際の会話内容をログから削除（引継ぎ時のエビデンス用だけに魚拓をしたため）
2026-02-14 キャッシュクリア データシートの`.gitignore`適応
2026-02-14 Usage追記
2026-02-14 アーカイブフォルダの作成
    旧い自動化対応のデータを手動アーカイブするフォルダを作成
    （今後`gottenitem_categorize`以外にも一時的な自動処理機能ができるのを想定）
2026-02-14 大幅改修・チートシート生成 その７
    TI製品番のデータシート検出精度を向上（残14品番）
2026-02-14 大幅改修・チートシート生成 その8-1
    かなり大規模かつ長期間の実装対応になりそうなのでいったん中間地点として全体をリファクタリング（PDCAのPとD）
    ### `./usage`フォルダ整理
    既存データ（サンプル回路提案：`./usage/74x**/`）と新規データ（チートシート：`./usage/cheatsheets/`）をフォルダ統合しカテゴリ・パーツごとのフォルダ分けに変更
    ### 全体のリファクタリング・指示更新
    既存データ(現時点の`main`ブランチ)と新規データ(`usage-renewal`ブランチ)で全体の整合性を保証
    - いったんすべてのスクリプトの動作とMarkdownの内
2026-02-14 大幅改修・チートシート生成 その8-2
    かなり大規模かつ長期間の実装対応になりそうなのでいったん中間地点として全体をリファクタリング（PDCAのC）
    - スクリプトの実行テスト
    - 将来計画(`purchase_plan`)で記載がなかったロジック番号を追加（前述の実行テストで生成）
    - 指示書更新
2026-02-14 大幅改修・チートシート生成 その9-1
    `74x181,182`のサンプルについては複数のロジック番号を用いるため、`A_combinated_samples`として新規フォルダに移動
    （指示更新の前にいったんコミットを分割）
2026-02-14 大幅改修・チートシート生成 その9-2
    `74x181,182`のサンプルについては複数のロジック番号を用いるため、`A_combinated_samples`という特殊なカテゴリに分類するよう指示を更新
2026-02-15 Usage自動化試作 その１
    データシートのオンライン自動参照ができそうなので試しに簡単なロジックゲートのデモ資料を自動作成してもらった
    まだまだ堅実性に改善の余地はあるけど、もう少しで実現はできそうな気はする
2026-02-15 大幅改修・チートシート生成＆Usage自動化試作 アーカイブログ作成-Feb.15
    明日以降の俺に任せるためのアーカイブログを念のためバックアップ
2026-05-30 PCBデモ回路生成機能実装 その１
2026-05-30 自動確認できるところを自動化
    以下の一次資料チェック項目を自動化して工数削減
    - usage対象とする実型番の決定
    - データシートの有無確認・参照設定
2026-05-30 一次資料チェック半自動化ツールの導入
    手動で数百のロジックICを確認するのが~~面倒~~手間なので、CopilotのAgentモードを使って半自動化するツールを実装してもらった
    - データシートを画像認識し、その結果 信憑性85%以上の項目をそのままCopilotによる自動採用, 85%未満の項目をUserによる目視確認で確認ロジックを分岐させて半自動化する仕組み
    - 活字化されているなら画像認識がちゃんと機能してるっぽいので、アナログスキャン書類でもない限りはほぼ自動化できたといってもよさそう
    - 上記の半自動化ツールの動
2026-05-30 PCBデモ回路生成機能実装 その２
2026-05-30 PCBデモ回路生成機能実装 その３
2026-05-30 PCBデモ回路生成機能実装 その４
2026-05-30 一次資料半自動チェック 一括処理
    自動化基準（信憑性85%以上）となった項目だけ一括でチェックを回すように
2026-05-30 Copilot指示強化（半自動チェックについて）
2026-05-30 Copilot指示強化（PCBデモ回路生成機能について）
2026-06-15 Agents指示書更新
2026-06-15 PCBデモ回路生成機能実装 その５
    流石に回路図自動生成は駄目そう
2026-06-15 データシート自動収集を試みようとした
